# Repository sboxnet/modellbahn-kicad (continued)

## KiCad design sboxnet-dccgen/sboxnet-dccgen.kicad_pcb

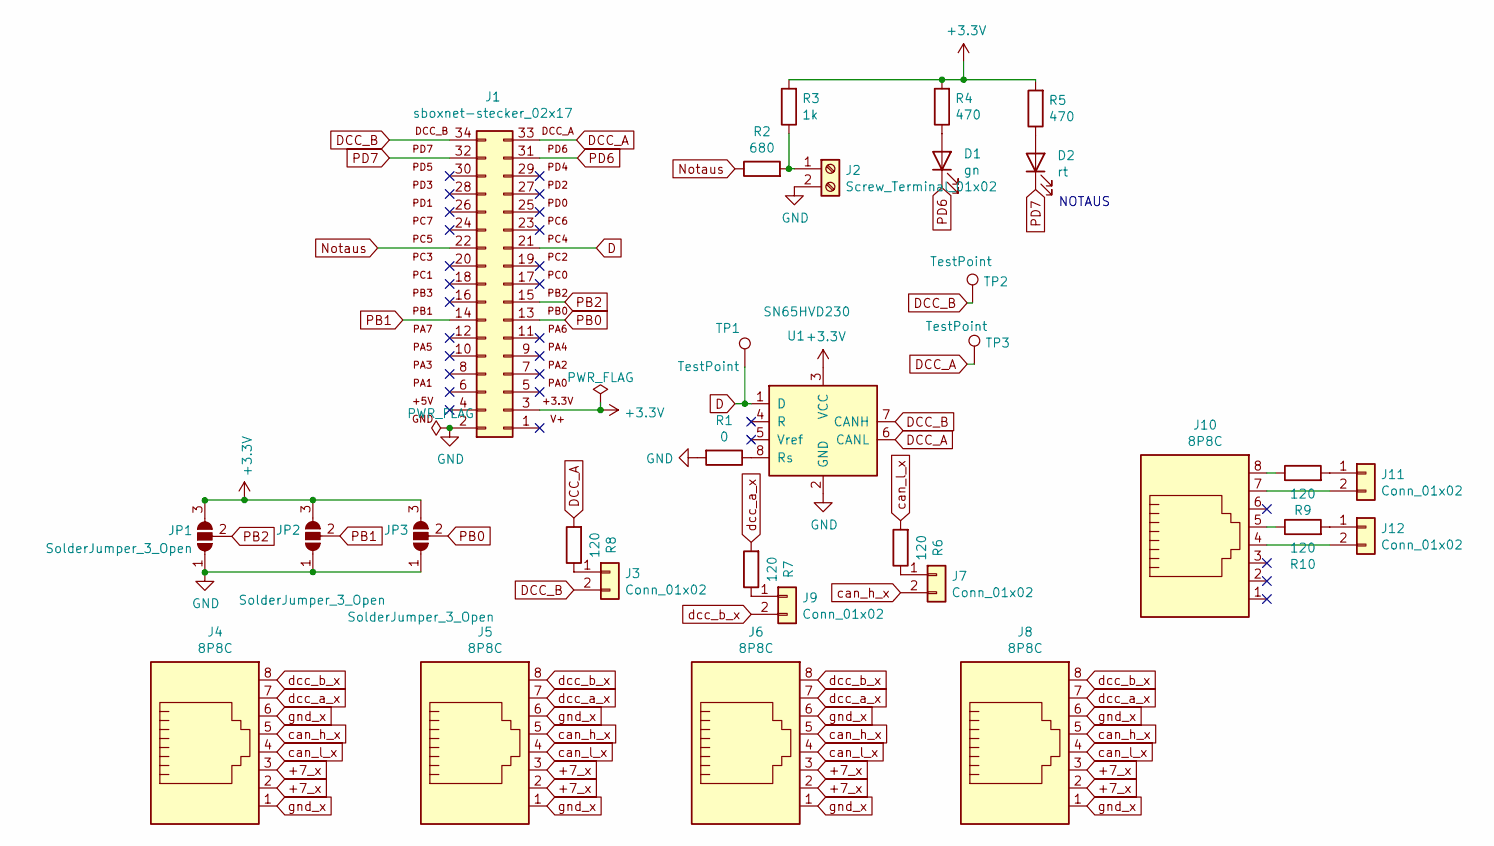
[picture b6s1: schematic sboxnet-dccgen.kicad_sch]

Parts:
D1: gn; LED_D3.0mm
D2: rt; LED_D3.0mm
J1: sboxnet-stecker_02x17; sboxnet-stecker-2x17
J2: Screw_Terminal_01x02; TerminalBlock_Altech_AK300-2_P5.00mm
J3, J7, J9, J11, J12: Conn_01x02; PinHeader_1x02_P2.54mm_Vertical
J4, J5, J6, J8, J10: 8P8C; 8p8c-mebp
JP1, JP2, JP3: SolderJumper_3_Open; SolderJumper-3_P1.3mm_Open_Pad1.0x1.5mm
R1: 0; R_1206_3216Metric
R2: 680; R_1206_3216Metric
R3: 1k; R_1206_3216Metric
R4, R5: 470; R_1206_3216Metric
R6, R7, R8, R9, R10: 120; R_1206_3216Metric
TP1, TP2, TP3: TestPoint; PinHeader_1x01_P2.54mm_Vertical
U1: SN65HVD230; SOIC-8_3.9x4.9mm_P1.27mm

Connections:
+3V3: J1.3, JP1.3 (B), JP2.3 (B), JP3.3 (B), R3.2, R4.2, R5.2, U1.3 (VCC); also elsewhere on the board
+7_x: J4.2, J4.3, J5.2, J5.3, J6.2, J6.3, J8.2, J8.3
D: J1.21, TP1.1, U1.1 (D)
DCC_A: J1.33, R8.2, TP3.1, U1.6 (CANL); also elsewhere on the board
DCC_B: J1.34, J3.2, TP2.1, U1.7 (CANH); also elsewhere on the board
GND: J1.2, J2.2, JP1.1 (A), JP2.1 (A), JP3.1 (A), R1.2, U1.2 (GND)
unnamed: D1.2 (A), R4.1
unnamed: D2.2 (A), R5.1
unnamed: J2.1, R2.2, R3.1
unnamed: J3.1, R8.1
unnamed: J7.1, R6.1
unnamed: J9.1, R7.1
unnamed: J10.4, J12.2
unnamed: J10.5, R10.1
unnamed: J10.7, J11.2
unnamed: J10.8, R9.1
unnamed: J11.1, R9.2
unnamed: J12.1, R10.2
unnamed: R1.1, U1.8 (Rs)
Notaus: J1.22, R2.1
PB0: J1.13, JP3.2 (C)
PB1: J1.14, JP2.2 (C)
PB2: J1.15, JP1.2 (C)
PD6: D1.1 (K), J1.31
PD7: D2.1 (K), J1.32 (PD7)
can_h_x: J4.5, J5.5, J6.5, J7.2, J8.5
can_l_x: J4.4, J5.4, J6.4, J8.4, R6.2
dcc_a_x: J4.7, J5.7, J6.7, J8.7, R7.2
dcc_b_x: J4.8, J5.8, J6.8, J8.8, J9.2
gnd_x: J4.1, J4.6, J5.1, J5.6, J6.1, J6.6, J8.1, J8.6

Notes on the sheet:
NOTAUS

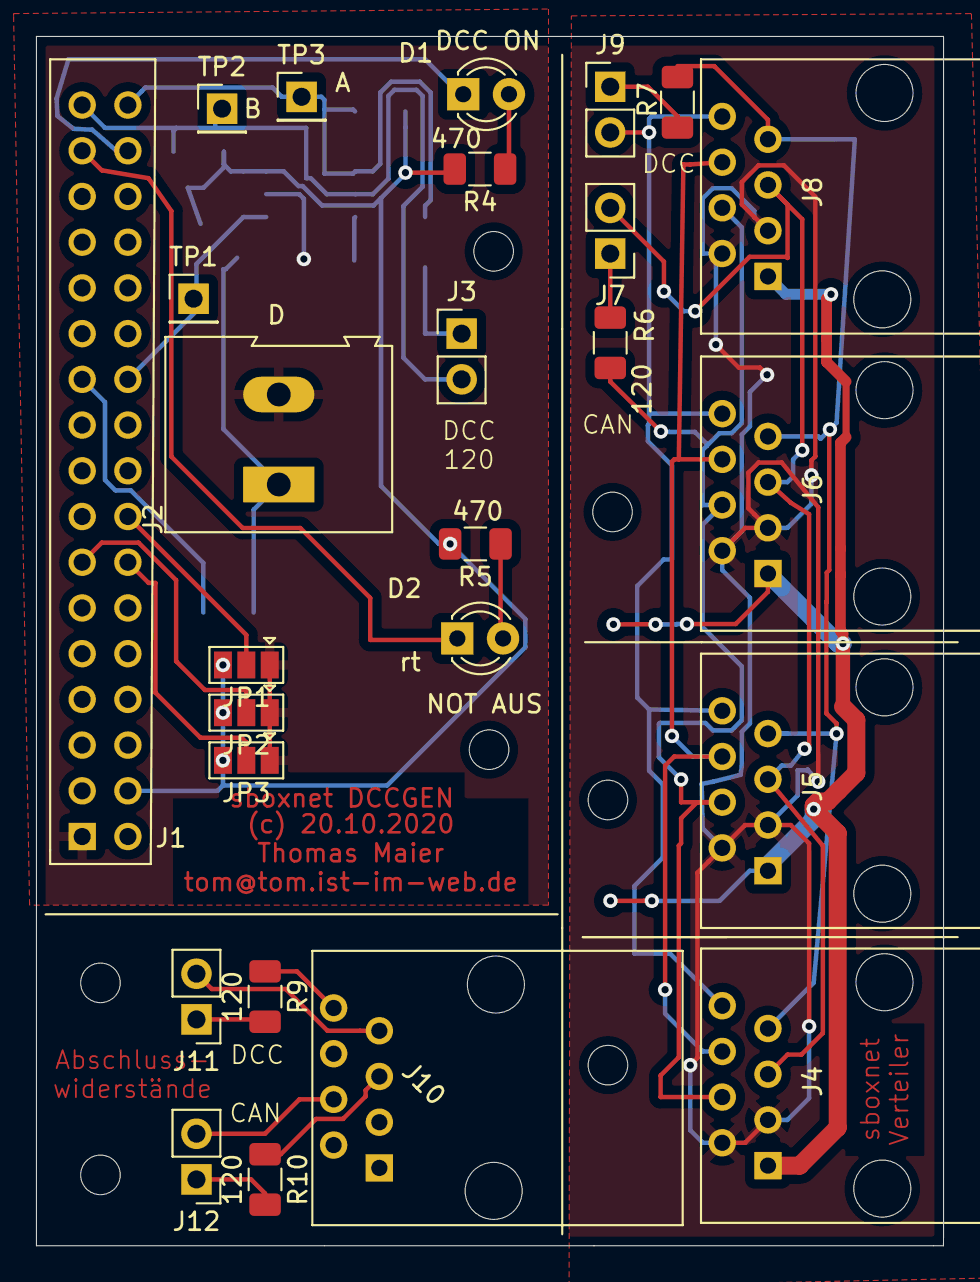
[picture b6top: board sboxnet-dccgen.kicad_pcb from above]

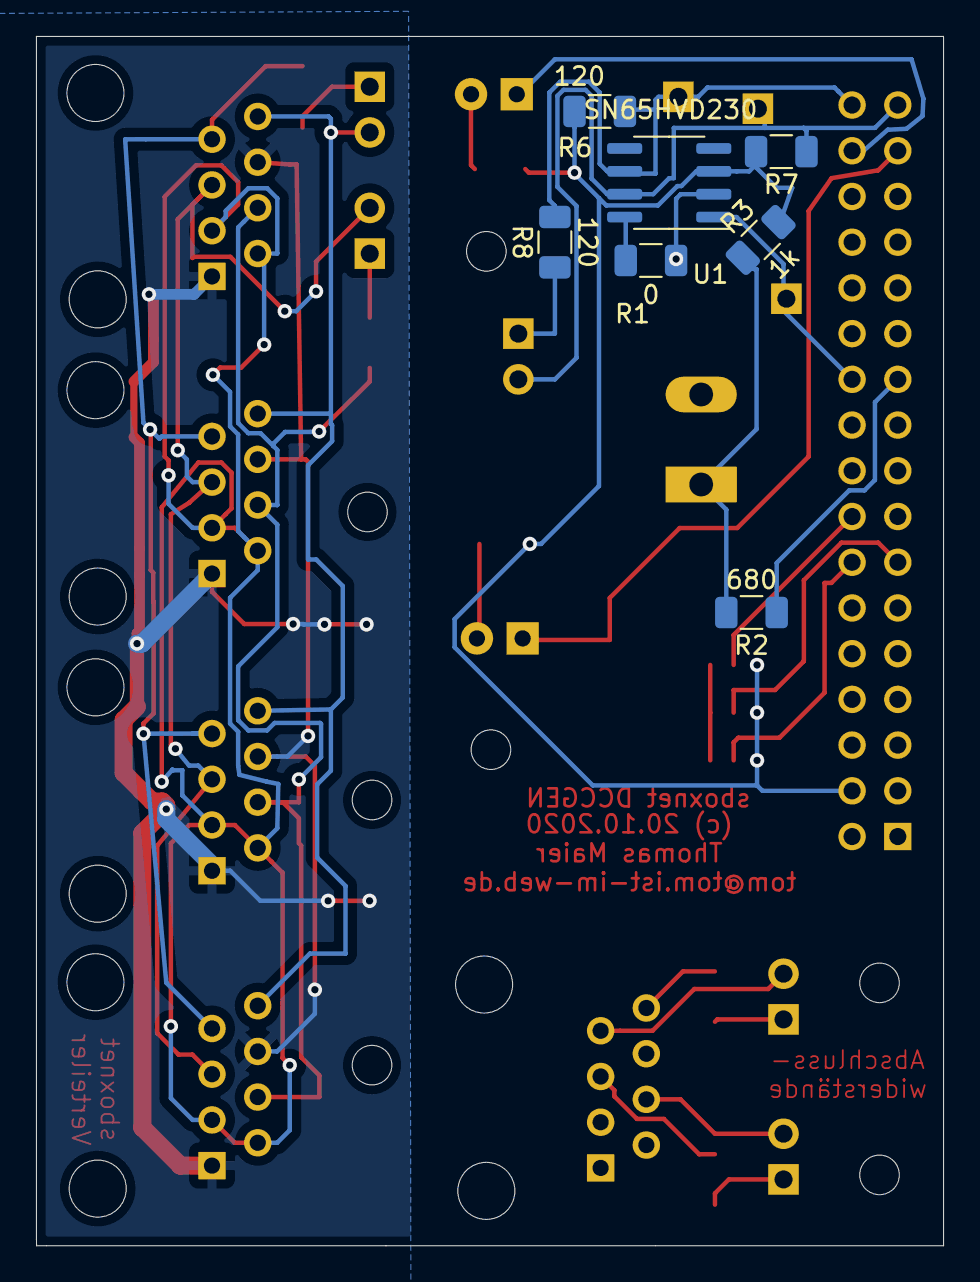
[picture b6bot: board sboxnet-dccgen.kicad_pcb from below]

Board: 2 copper layers, 50.4 x 67.2 mm, 33 parts (7 on the bottom side), 30 nets.

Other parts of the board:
R6#2, R7#2: 120; R_1206_3216Metric

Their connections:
+3V3: R6#2.2, R7#2.2; also elsewhere on the board
DCC_A: R6#2.1; also elsewhere on the board
DCC_B: R7#2.1; also elsewhere on the board

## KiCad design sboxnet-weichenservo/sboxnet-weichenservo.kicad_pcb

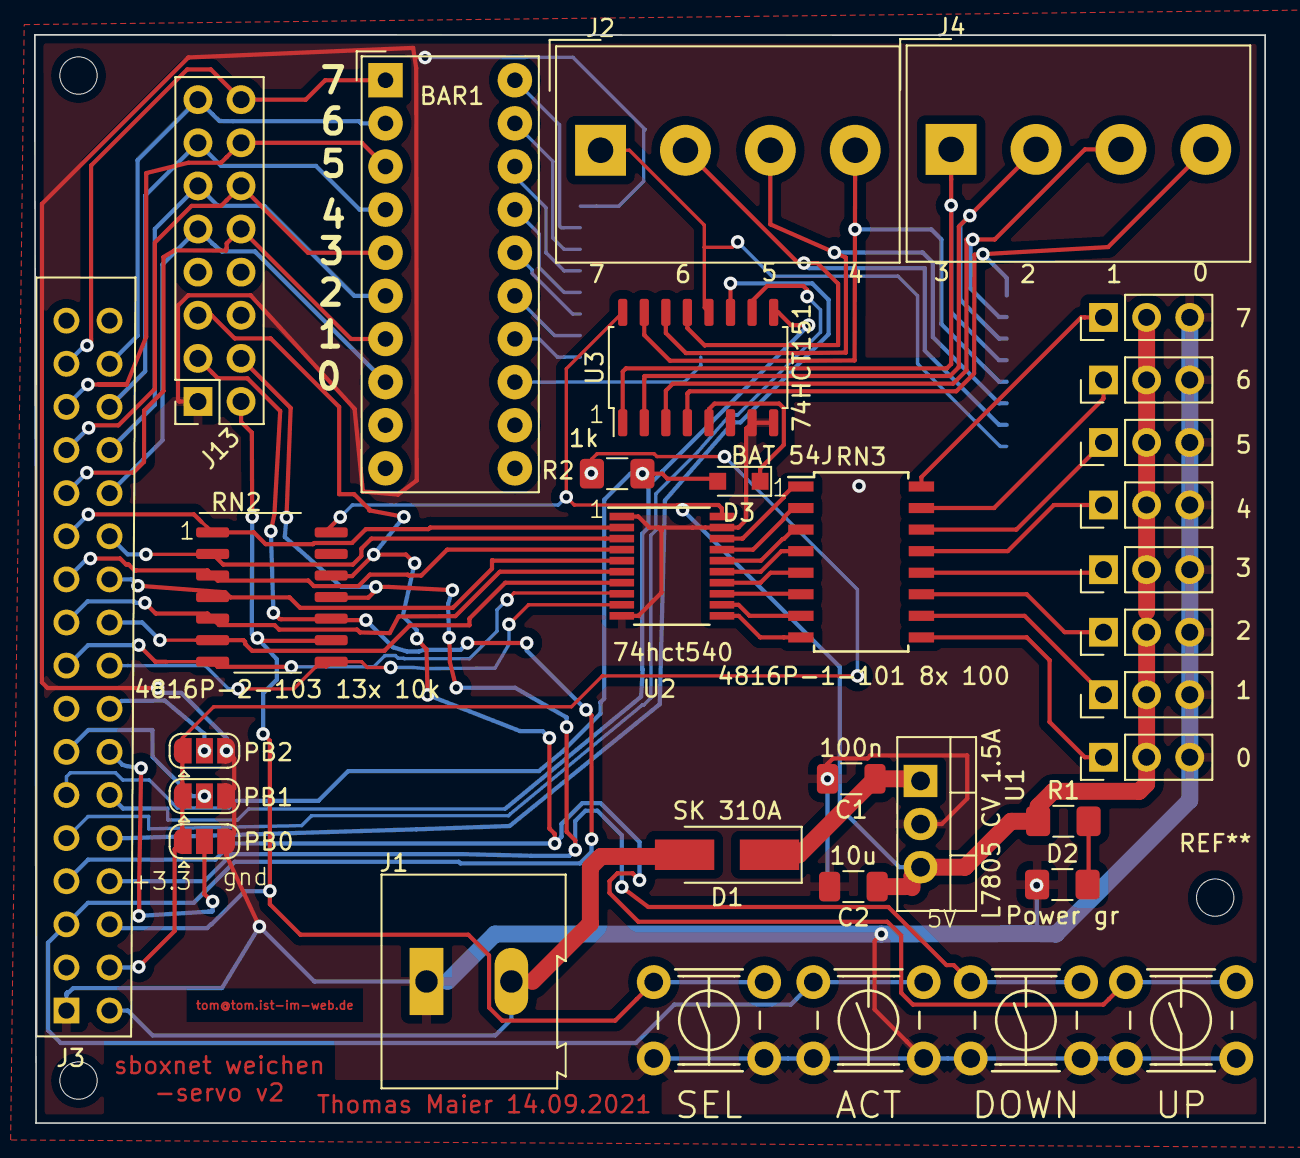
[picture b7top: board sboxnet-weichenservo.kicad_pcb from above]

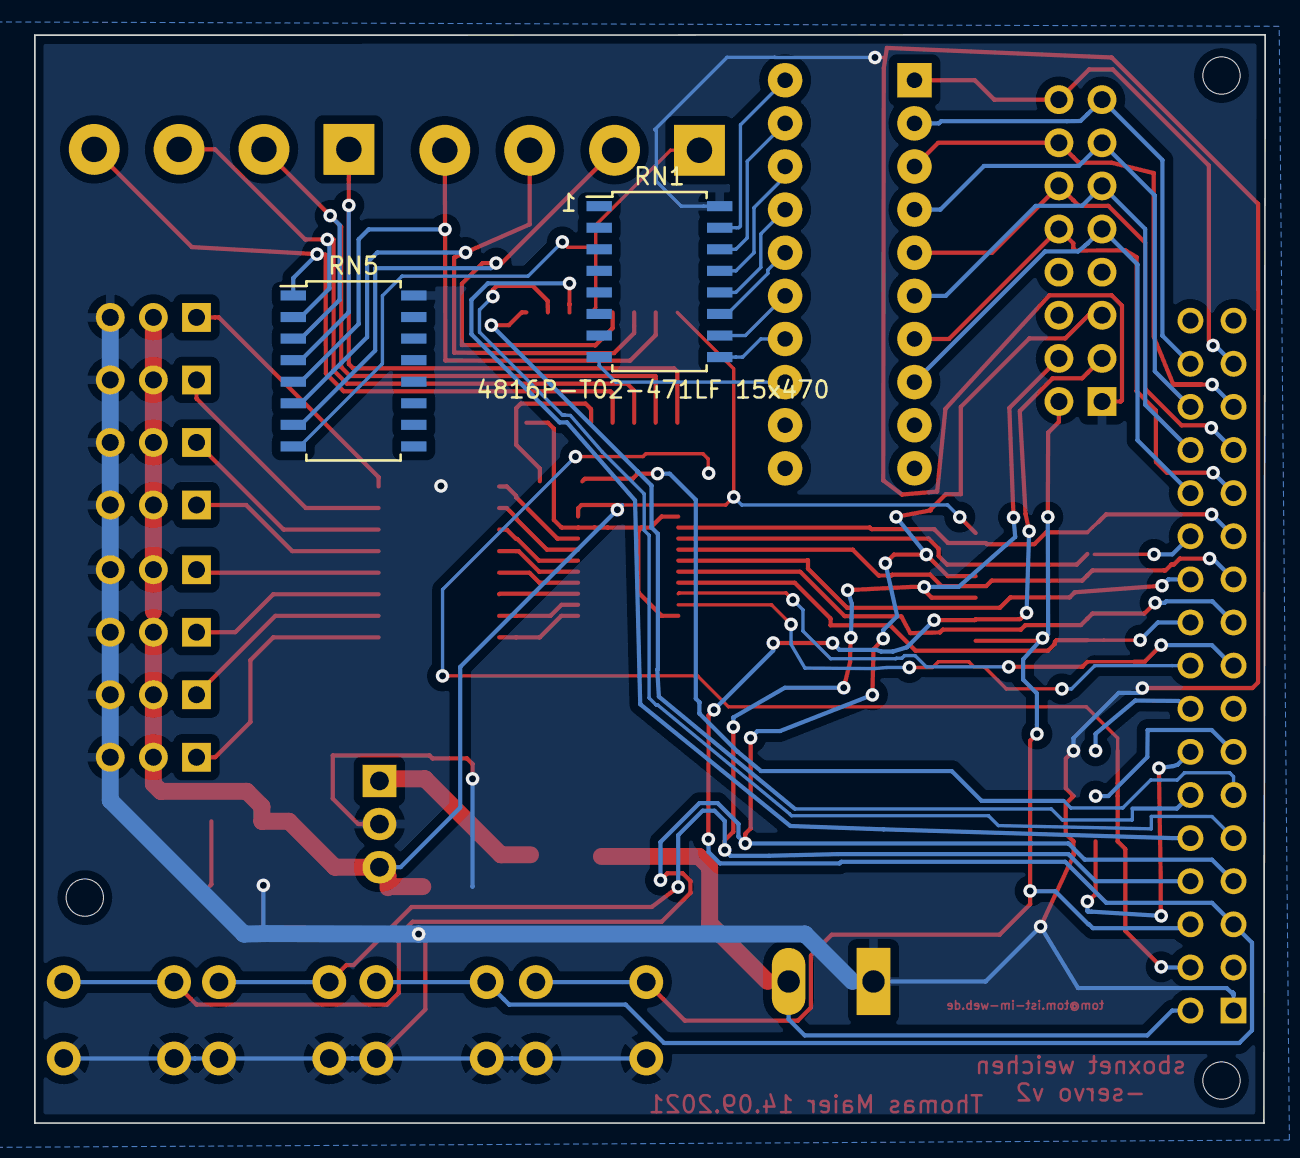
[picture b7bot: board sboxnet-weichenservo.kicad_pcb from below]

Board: 2 copper layers, 72.5 x 64.1 mm, 35 parts (2 on the bottom side), 66 nets.

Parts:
BAR1: HDSP-4830_2 10x LED; HDSP-4830
C1: 100n; C_1206_3216Metric
C2: 10u; C_1206_3216Metric
D1: SK 310A; D_SMA_Handsoldering
D2: Power gr; R_1206_3216Metric_Pad1.42x1.75mm_HandSolder
D3: BAT 54J NXP; D_SOD-323_HandSoldering
J1: Screw_Terminal_01x02; TerminalBlock_Altech_AK300-2_P5.00mm
J2, J4: Screw_Terminal_01x04; Altech_AK300_1x04_P5.00mm_45-Degree
J3: Conn_02x17_Odd_Even; sboxnet-stecker-2x17
J5, J6, J7, J8, J9, J10, J11, J12: Conn_01x03_Male; PinHeader_1x03_P2.54mm_Vertical
J13: Conn_02x08_Top_Bottom; PinSocket_2x08_P2.54mm_Vertical
JP1, JP2, JP3: SolderJumper_3_Open; SolderJumper-3_P1.3mm_Open_RoundedPad1.0x1.5mm
R1: 1k; R_1206_3216Metric_Pad1.42x1.75mm_HandSolder
R2: 100; R_1206_3216Metric_Pad1.42x1.75mm_HandSolder
RN1: 4816P-T02-471LF 15x470; SOIC-16W_5.3x10.2mm_P1.27mm
RN2: 4816P-2-103 13x 10k; soic-14-8-6
RN3: 4816P-1-101 8x 100; SOIC-16W_5.3x10.2mm_P1.27mm
RN5: 4816P-T02-103 15x1k; SOIC-16W_5.3x10.2mm_P1.27mm
SW1: UP; JTP-1130
SW2: DOWN; JTP-1130
SW3: ACT; JTP-1130
SW4: SEL; JTP-1130
U1: L7805 CV 1.5A; TO-220-3_Vertical
U2: 74hct540; TSSOP-20_4.4x6.5mm_P0.65mm
U3: 74HCT151; SOIC-16_4.55x10.3mm_P1.27mm

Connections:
+3V3: J3.3, JP1.1 (A), JP2.1 (A), JP3.1 (A), R2.2
+5V: C2.1, J5.2, J6.2, J7.2, J8.2, J9.2, J10.2, J11.2, J12.2, R1.1, RN2.14 (common), U1.3 (OUT), U2.20 (VCC), U3.16 (VCC)
/L0: BAR1.20 (K), RN1.15 (R15)
/L1: BAR1.19 (K), RN1.14 (R14)
/L2: BAR1.18 (K), RN1.13 (R13)
/L3: BAR1.17 (K), RN1.12 (R12)
/L4: BAR1.16 (K), RN1.11 (R11)
/L5: BAR1.15 (K), RN1.10 (R10)
/L6: BAR1.14 (K), RN1.9 (R9)
/L7: BAR1.13 (K), RN1.8 (R8)
/a1: J4.4, RN5.1 (R1), U3.4 (I0)
/a2: J4.3, RN5.2 (R2), U3.3 (I1)
/a3: J4.2, RN5.3 (R3), U3.2 (I2)
/a4: J4.1, RN5.4 (R4), U3.1 (I3)
/a5: J2.4, RN5.5 (R5), U3.15 (I4)
/a6: J2.3, RN5.6 (R6), U3.14 (I5)
/a7: J2.2, RN5.7 (R7), U3.13 (I6)
/a8: J2.1, RN5.8 (R8), U3.12 (I7)
GND: C1.2, C2.2, D2.1 (K), J1.1, J3.2, J5.3, J6.3, J7.3, J8.3, J9.3, J10.3, J11.3, J12.3, J13.1, JP1.3 (B), JP2.3 (B), JP3.3 (B), RN1.16 (common), RN5.16 (common), SW1.1, SW2.1, SW3.1, SW4.1, U1.2 (GND), U2.1 (G1), U2.10 (GND), U2.19 (G2), U3.7 (~E), U3.8 (GND)
unnamed: C1.1, D1.1 (K), U1.1 (IN)
unnamed: D1.2 (A), J1.2, J3.1
unnamed: D2.2 (A), R1.2
unnamed: D3.1 (K), U3.5 (Q)
unnamed: J5.1, RN3.9 (R8.2)
unnamed: J6.1, RN3.10 (R7.2)
unnamed: J7.1, RN3.11 (R6.2)
unnamed: J8.1, RN3.12 (R5.2)
unnamed: J9.1, RN3.13 (R4.2)
unnamed: J10.1, RN3.14 (R3.2)
unnamed: J11.1, RN3.15 (R2.2)
unnamed: J12.1, RN3.16 (R1.2)
unnamed: RN3.1 (R1.1), U2.18 (Y0)
unnamed: RN3.2 (R2.1), U2.17 (Y1)
unnamed: RN3.3 (R3.1), U2.16 (Y2)
unnamed: RN3.4 (R4.1), U2.15 (Y3)
unnamed: RN3.5 (R5.1), U2.14 (Y4)
unnamed: RN3.6 (R6.1), U2.13 (Y5)
unnamed: RN3.7 (R7.1), U2.12 (Y6)
unnamed: RN3.8 (R8.1), U2.11 (Y7)
PA0: J3.5, J13.2, RN2.9 (R9), SW4.2
PA1: J3.6, J13.3, RN2.10 (R10), SW3.2
PA2: J3.7, J13.4, RN2.11 (R11), SW2.2
PA3: J3.8, J13.5, RN2.12 (R12), SW1.2
PA4: J3.9, U3.11 (S0)
PA5: J3.10, U3.10 (S1)
PA6: J3.11, U3.9 (S2)
PA7: D3.2 (A), J3.12, R2.1
PB0: J3.13, JP2.2 (C)
PB1: J3.14, JP3.2 (C)
PB2: J3.15, JP1.2 (C)
PC0: J3.17, RN2.8 (R8), U2.9 (A7)
PC1: J3.18, RN2.7 (R7), U2.8 (A6)
PC2: J3.19, RN2.6 (R6), U2.7 (A5)
PC3: J3.20, RN2.5 (R5), U2.6 (A4)
PC4: J3.21, RN2.4 (R4), U2.5 (A3)
PC5: J3.22, RN2.3 (R3), U2.4 (A2)
PC6: J3.23, RN2.2 (R2), U2.3 (A1)
PC7: J3.24, RN2.1 (R1), U2.2 (A0)
PD0: BAR1.8 (A), J3.25, J13.9
PD1: BAR1.7 (A), J3.26, J13.10
PD2: BAR1.6 (A), J3.27, J13.11
PD3: BAR1.5 (A), J3.28, J13.12
PD4: BAR1.4 (A), J3.29, J13.13
PD5: BAR1.3 (A), J3.30, J13.14
PD6: BAR1.2 (A), J3.31, J13.15
PD7: BAR1.1 (A), J3.32, J13.16

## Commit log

2021-08-01 readme
2021-08-01 init
2021-08-13 added weichen-servo-ctrl
2021-08-13 mit weichen-servo-ctrl
2021-08-20 weichenservo mit Modulkennung
2021-08-20 fixed
2021-08-22 weichen-servo mit Mounting Holes
2021-09-14 changed hole of sboxnet-stecker to 0.9
2021-09-15 v2-sboxnet-weichenservo
2021-10-04 angepasst sboxnet stecker 0.95 Hole
2021-11-01 neuer DCCGEN mit sboxnet Verteiler und Abschlusswiderstanden
2021-11-14 dccgen bestellt
2021-11-15 fix dccgen layout
2021-11-15 erneut dccgen
2021-12-08 booster modul mit l6206 dip
2022-01-16 Booster Output angepasst nach test
2022-01-16 korrigiert Charge Pump for DIL
2022-02-03 booster l6206 parallel geschaltet
2022-02-21 IN1 and IN2 fixed
2022-03-08 kicad 6
2022-04-19 entwurf fuer sboxnet-booster
2022-06-19 booster testpoint pc7, circuit board for out* pins to 1mm
2022-06-20 weichenservo mit PBx und Rueckmeldung pull up
2022-06-21 dccgen Modul
2022-07-26 kleiner booster
2022-07-27 shrink booster
2022-07-31 sboxnet-booster-v1
2022-08-19 correct sboxnet-booster-v2
2022-08-19 backup as v2
2022-08-21 correct l6206 footprint, notaus as terminal block
2022-08-21 bat54s
2022-10-04 kicad 5 -> 6
2022-10-04 QS4A_0303S1.5UP footprint
2022-10-05 sboxnet-gbm2
2022-10-05 gpio-usb
2022-10-17 v2-sboxnet-booster
2022-12-29 cleanup
2022-12-29 v4-sboxnet-modul.kicad_pro
2023-01-04 sboxnet-modul v5
2023-06-29 gbm2-schema
2023-07-08 sboxnet_booster smd v3
2023-07-17 sboxnet-booster-v3
2023-07-17 v3 files
2023-08-05 sboxnet schema
2023-08-29 sobxnet modul v5
2023-08-29 restruktur
2023-08-29 sboxnet modul v6.1
2023-08-29 sboxnet modul v6.2
2023-08-31 sboxnet modul V6
2023-09-01 sboxnet Modul v6 with some mods
2023-09-03 sboxnet Modul v6 fertig
